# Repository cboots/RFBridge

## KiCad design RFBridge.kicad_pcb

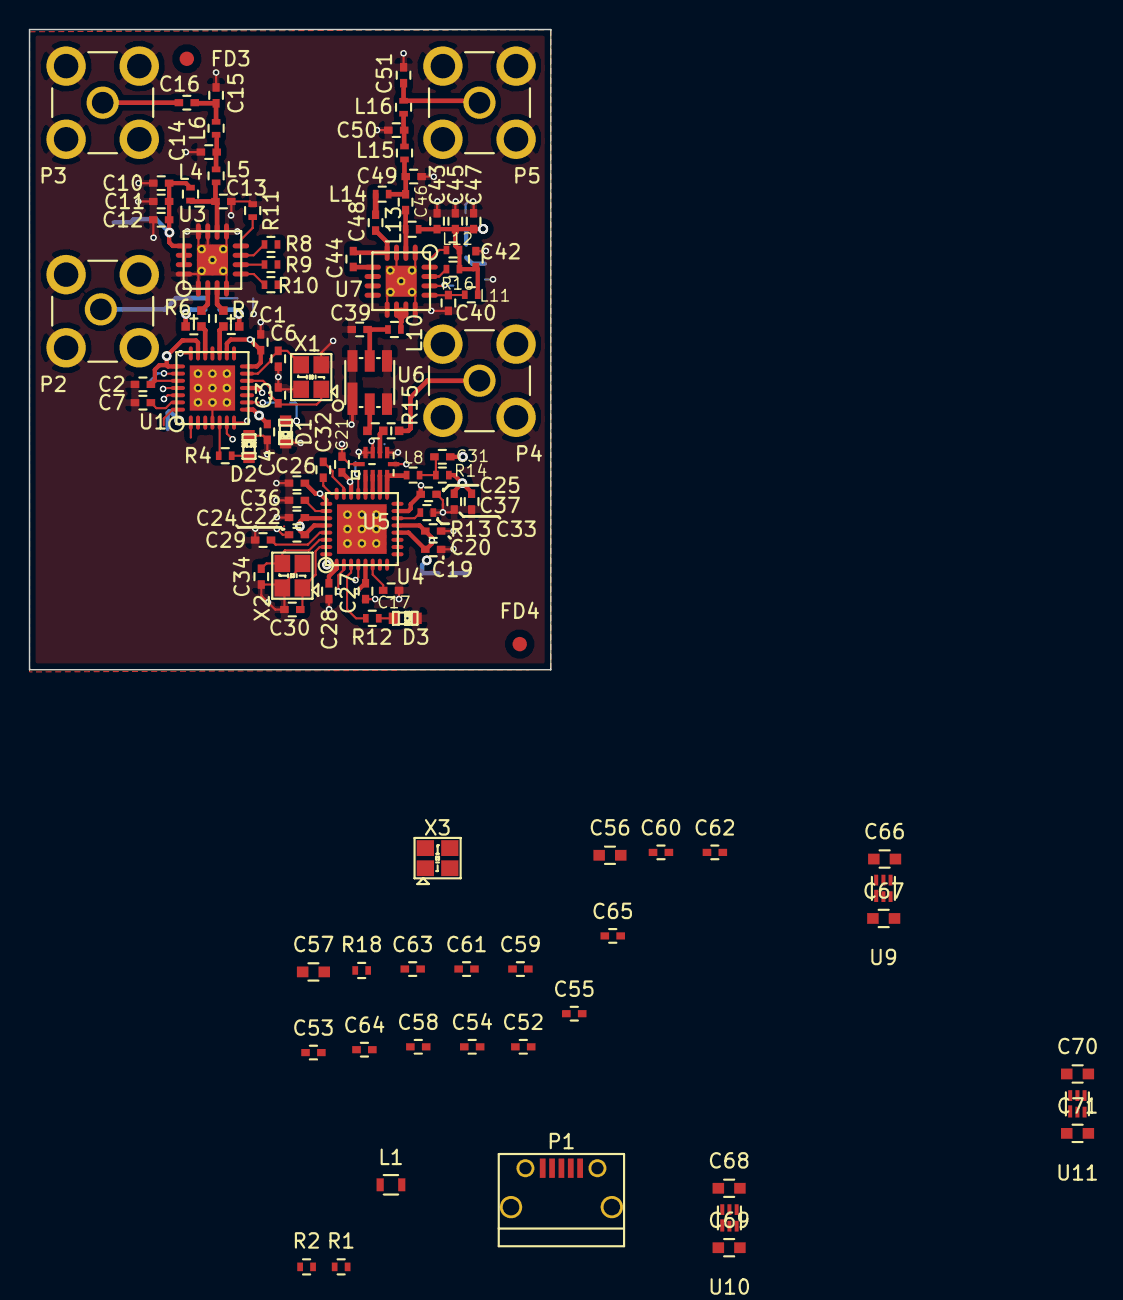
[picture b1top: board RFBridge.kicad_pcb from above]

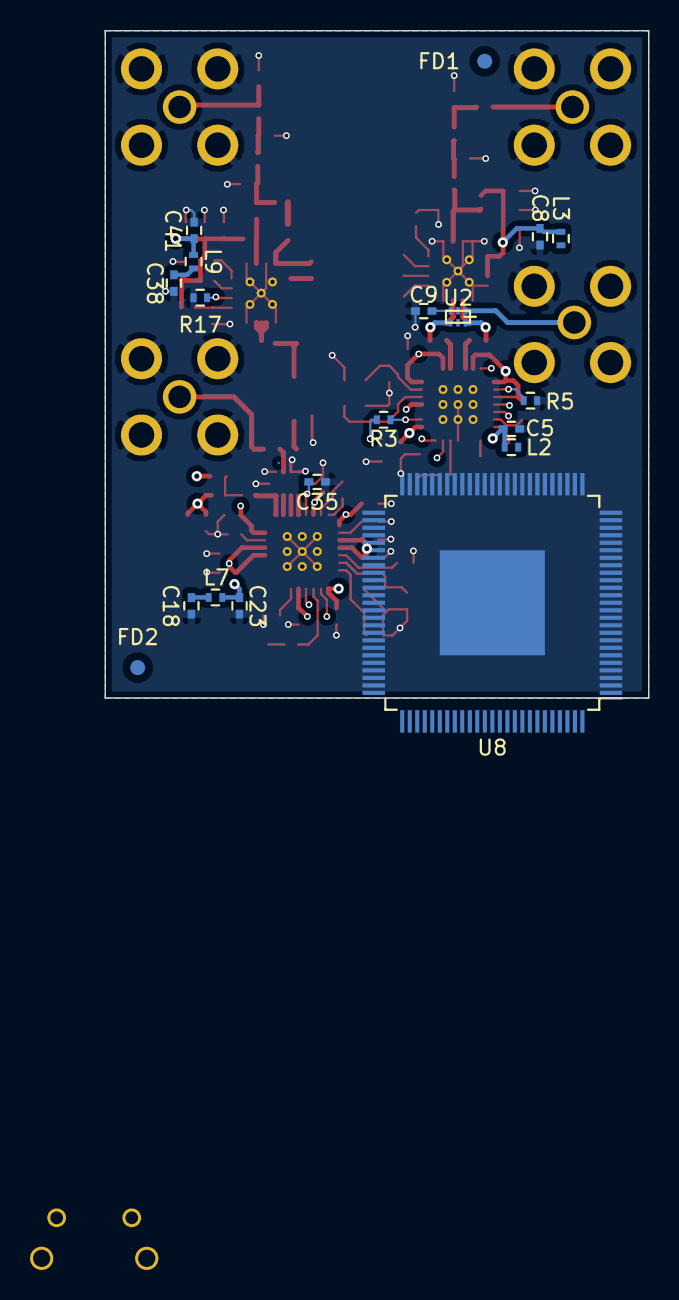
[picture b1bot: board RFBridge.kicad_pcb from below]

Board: 4 copper layers, 36.2 x 44.4 mm, 131 parts (17 on the bottom side), 80 nets.

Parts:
C1, C2, C4, C7, C54, C55, C58, C59, C60, C61, C62, C63, C64, C65: 0.1u; C_0402
C3, C6, C12, C30, C34, C44, C48, C52, C53: 12p; C_0402
C5, C8: 2.2u; C_0402
C9: 6.8p; C_0402
C10, C43: 1u; C_0402
C11, C47: 1n; C_0402
C13, C14: 2.2p; C_0402
C15: 0.2p; C_0402
C16: 18p; C_0402
C17: 220n; C_0402
C18: 100n; C_0402
C19, C20, C21, C22, C24, C25, C26, C27, C28, C29, C36: 47n; C_0402
C23: 2u2; C_0402
C31: 33p; C_0402
C32: 1.8n; C_0402
C33, C35: 10n; C_0402
C37: 100p; C_0402
C38: 220p; C_0402
C39: 0.8p; C_0402
C40: 15p; C_0402
C41: 10u; C_0402
C42: 27p; C_0402
C45, C46: 47p; C_0402
C49: 3.3p; C_0402
C50: 7.5p; C_0402
C51: 9.1n; C_0402
C56, C57: 10u; C_0603
C66, C67, C68, C69, C70, C71: 1u; C_0603
D1, D2, D3: LED; LED-0603
FD1, FD2: FIDUCIAL; Fiducial_1mm_Dia_2.54mm_Outer_CopperBottom
FD3, FD4: FIDUCIAL; Fiducial_1mm_Dia_2.54mm_Outer_CopperTop
L1: BLM18PG600SN1D; R_0603
L2, L3, L7: FERRITE BEAD; R_0402
L4: 4.7n; R_0402
L5: 1n; R_0402
L6: 2n; R_0402
L8: 8.2n; R_0402
L9: 11n; R_0402
L10: 10n; R_0402
L11: 1.5n; R_0402
L12: 15n; R_0402
L13: 22n; R_0402
L14: 7.5n; R_0402
L15: 2.9n; R_0402
L16: 9.1n; R_0402
P1: USB_OTG; USB_Micro-B
P2, P3, P4, P5: BNC; SMB_Straight
R1, R2: 33; R_0402
R3, R4, R12: 2k; R_0402
R5, R13: 56k; R_0402
R6: 0; R3_RH_0402
R7: 0; R3_LH_0402
R8, R9, R10, R18: 10k; R_0402
R11: 3.9k; R_0402
R14: 10; R_0402
R15: R3-S; R3_S_0402
R16: 47; R_0402
R17: 3.3k; R_0402
U1: CC2520; RHD_S-PVQFN-N28
U2: LDB182G4520C-110; LDB18
U3: CC2592; RGV_S-PVQFN-N16
U4: CC1200; RHB_S-PVQFN-N32
U5: 0900PC15J0013
U6: EPCOS_B3588; DCC6C
U7: CC1190; RGV_S-PVQFN-N16
U8: XMC4500F100; LQFP-100-1EP_14x14mm_Pitch0.5mm
U9, U10, U11: TPS727; S-PWSON-N6
X1, X2: FA-20H32.0000MF20X-K3; FA-20H
X3: FA-20H24.0000MF20Z-K3; FA-20H

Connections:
+5VUSB: L1.2, U8.10
/2G4Radio/ANT1_50: C13.1, L4.1, L5.1, U3.10
/2G4Radio/ANT2_50: C14.1, L5.2, L6.1
/2G4Radio/ANT3_50: C15.1, C16.2, L6.2
/2G4Radio/ANT4_50: C16.1, P3.1
/2G4Radio/ANT5_50: P2.1, U2.1
/2G4Radio/MISO: U1.1, U4.9
/2G4Radio/MOSI: U1.2, U4.7
/2G4Radio/RF1_N: R6.1, U3.2
/2G4Radio/RF1_P: R7.1, U3.3
/2G4Radio/RF2_N: R6.3, U2.6
/2G4Radio/RF2_P: R7.3, U2.4
/2G4Radio/RF_N: R6.2, U1.19
/2G4Radio/RF_P: R7.2, U1.17
/2G4Radio/VDD_CC2520_ISO: C1.1, C2.1, C4.1, C5.1, L2.1, U1.8, U1.11, U1.14, U1.16, U1.20, U1.22, U1.24
/2G4Radio/VDD_CC2592_ISO: C8.1, C10.1, C11.1, C12.1, L3.2, L4.2, U3.13, U3.14, U3.15
/900MRadio/ANT1_50: R15.2, U5.7
/900MRadio/ANT2_50: R15.1, U6.2
/900MRadio/ANT3_50: P4.1, R15.3
/900MRadio/ANT4_50: C39.1, L10.1, U6.5
/900MRadio/ANT5_50: L10.2, U7.10, U7.11
/900MRadio/ANT6_50: C46.1, C49.2, L14.2, L15.1
/900MRadio/ANT7_50: C50.2, L15.2, L16.1
/900MRadio/ANT8_50: C51.2, L16.2, P5.1
/900MRadio/LNA_IN_50: C44.1, U7.5
/900MRadio/LNA_N: U4.20, U5.1
/900MRadio/LNA_P: U4.19, U5.2
/900MRadio/PA: L8.2, U4.17, U5.4
/900MRadio/PA_OUT_50: C46.2, L13.2, U7.2
/900MRadio/TRX: U4.18, U5.3
/900MRadio/TR_SW_50: C44.2, C48.2, U7.4
/900MRadio/VDD_CC1120_ISO: C19.1, C20.1, C21.1, C22.1, C23.1, C24.1, C25.1, C26.1, C27.1, C28.1, C31.1, C33.1, C37.1, L7.2, R14.1, U4.1, U4.5, U4.12, U4.13, U4.15, U4.22, U4.25, U4.27, U4.28
/900MRadio/VDD_CC1190: C38.2, L9.1
/900MRadio/VDD_CC1190_ISO: C41.2, C42.2, C43.2, C45.2, C47.2, L9.2, L11.2, L12.1, L13.1, R16.1
/900MRadio/VDD_CC1200: C18.1, C71.1, L7.1, U11.1
/LDO3V3_CC1200/VIN: C70.1, U11.6
/LDO3V3_CC2520/VIN: C68.1, U10.6
/LDO3V3_CC2520/VOUT: C69.1, U10.1
/LDO3V3_MCU/VIN: C66.1, U9.6
/XMC4500/CC1200_GPIO3: R12.1, U4.3
/XMC4500/CC2520_FIFO: R3.1, U1.9
/XMC4500/CC2520_SFD: R4.1, U1.5
/XMC4500/RADIO_SCLK: U1.28, U4.8
/XMC4500/USB_N: R1.1, U8.8
/XMC4500/USB_P: R2.1, U8.9
/XMC4500/VDD_MCU: C54.1, C55.1, C56.1, C57.1, C58.1, C59.1, C60.1, C61.1, C62.1, C63.1, C64.1, C65.1, C67.1, U8.11, U8.12, U8.17, U8.33, U8.35, U8.42, U8.43, U8.60, U8.64, U8.86, U8.87, U9.1
GND: C1.2, C2.2, C3.2, C4.2, C5.2, C6.2, C7.2, C8.2, C9.1, C10.2, C11.2, C12.2, C13.2, C14.2, C15.2, C17.2, C18.2, C19.2, C20.2, C21.2, C22.2, C23.2, C24.2, C25.2, C26.2, C27.2, C28.2, C29.2, C30.2, C33.2, C34.2, C35.2, C36.2, C37.2, C38.1, C39.2, C40.1, C41.1, C42.1, C43.1, C45.1, C47.1, C49.1, C50.1, C51.1, C52.2, C53.2, C54.2, C55.2, C56.2, C57.2, C58.2, C59.2, C60.2, C61.2, C62.2, C63.2, C64.2, C65.2, C66.2, C67.2, C68.2, C69.2, C70.2, C71.2, D1.1, D2.1, D3.1, P1.5, P1.6, P2.2, P3.2, P4.2, P5.2, R5.2, R11.2, R13.2, R17.2, R18.2, U1.4, U1.EP, U3.1, U3.4, U3.9, U3.11, U3.12, U3.16, U3.EP, U4.EP, U5.5, U5.6, U5.8, U5.9, U5.10, U6.1, U6.3, U6.4, U6.6, U7.1, U7.3, U7.9, U7.12, U7.EP, U8.32, U8.34, U8.59, U8.63, U8.101, U9.3, U10.3, U11.3, X1.2, X1.4, X2.2, X2.4, X3.2, X3.4
unnamed: C3.1, U1.12, X1.1
unnamed: C6.1, U1.13, X1.3
unnamed: C7.1, U1.27
unnamed: C9.2, U2.3
unnamed: C17.1, U4.6
unnamed: C29.1, U4.29
unnamed: C30.1, U4.31, X2.1
unnamed: C31.2, L8.1, R14.2
unnamed: C32.1, U4.24
unnamed: C32.2, U4.23
unnamed: C34.1, U4.30, X2.3
unnamed: C35.1, U4.21
unnamed: C36.1, U4.26
unnamed: C40.2, L11.1, U7.13
unnamed: C48.1, L14.1
unnamed: C52.1, U8.61, X3.1
unnamed: C53.1, U8.62, X3.3
unnamed: D1.2, R3.2
unnamed: D2.2, R4.2
unnamed: D3.2, R12.2
unnamed: L1.1, P1.1
unnamed: L12.2, U7.16
unnamed: P1.2, R1.2
unnamed: P1.3, R2.2
unnamed: R5.1, U1.23
unnamed: R8.1, U3.7
unnamed: R9.1, U3.6
unnamed: R10.1, U3.5
unnamed: R11.1, U3.8
unnamed: R13.1, U4.14
unnamed: R16.2, U7.15
unnamed: R17.1, U7.14
unnamed: R18.1, U8.15

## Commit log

2015-07-04 Initial schematic
2015-07-04 Updated library references
2015-07-06 added some radio components.
2015-07-07 Added more RF components
2015-07-08 Added baluns
2015-07-11 Finished schematic of 2.4GHz and 900MHz radios
2015-07-12 Updated layout
2015-07-12 Fixed broken AVDD reference.
    Routed 2.4GHz radio.
2015-07-12 Mostly finished up 900MHz routing.
2015-07-12 Silk cleanup and some more routing finessing.
2015-07-13 Compressed design a bit.
2015-07-29 Added XMC4500.sch
2015-08-02 Added capacitors for XMC chip, diagram of power tree, and more connectors.
2015-08-09 Added 3.3V LDO
2015-08-09 Updated footprints
2015-08-10 Added barrel jack and ideal diode circuit
